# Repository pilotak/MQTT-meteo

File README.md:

# MQTT-meteo
STM32F103C8 (BluePill) based weather station. It can be either populated with Ethernet *(ENC28J60)* od WiFi *(ESP8266-01S)* module.

More info soon.

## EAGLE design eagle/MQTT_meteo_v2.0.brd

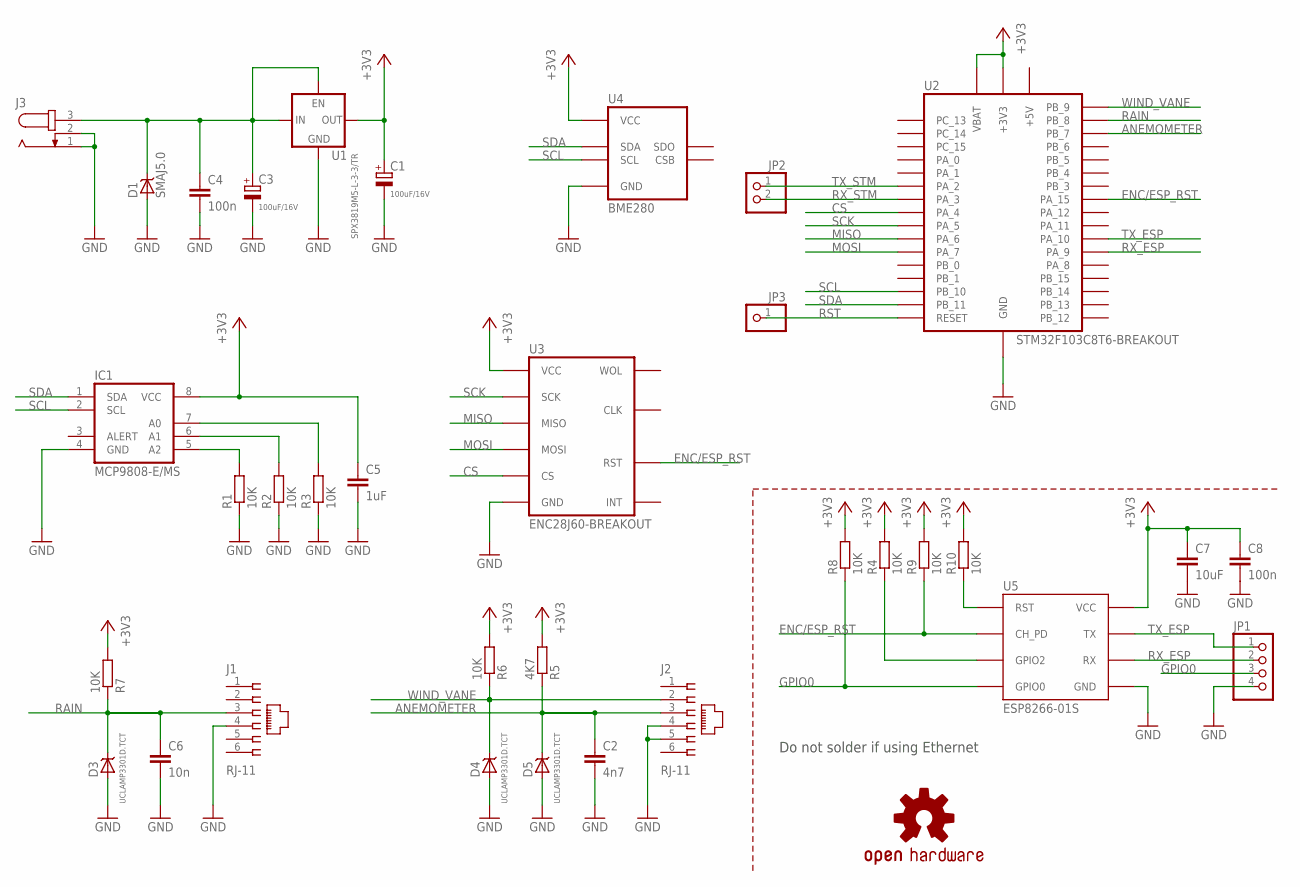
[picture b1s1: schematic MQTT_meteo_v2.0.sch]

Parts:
C1, C3: 100uF/16V; E2-5
C2: 4n7; C0805
C4, C8: 100n; C0805
C5: 1uF; C0805
C6: 10n; C0805
C7: 10uF; C0805
D1: SMAJ5.0; DO214AC
D3, D4, D5: UCLAMP3301D.TCT; SOD323
IC1: MCP9808-E/MS; MSOP8
J1, J2: RJ-11; 615006138421
J3: JACK-PLUG1; SPC4078
JP1: PINHD-1X4; 1X04
JP2: PINHD-1X2; 1X02
JP3: PINHD-1X01_2.54-90°; 1X01/90
LOGO1: OSHW-LOGOM-COPPER; OSHW-LOGO-M_COPPER
R1, R2, R3, R4, R6, R7, R8, R9, R10: 10K; R0805
R5: 4K7; R0805
U1: SPX3819M5-L-3-3/TR; SOT23-5
U2: STM32F103C8T6-BREAKOUT; STM32F103C8T6
U3: ENC28J60-BREAKOUT; ENC28J60
U4: BME280; BM*280
U5: ESP8266-01S; ESP-01

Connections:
+3V3: C1.+, C5.1, C7.1, C8.1, IC1.8 (VCC), R4.2, R5.2, R6.2, R7.2, R8.2, R9.2, R10.2, U1.5 (VOUT), U2.+3V3, U2.+3V3@1 (+3V3), U2.VBAT, U3.VCC, U4.VCC, U5.VCC
+5V: U2.+5V
ANEMOMETER: C2.1, D5.C, J2.3, R5.1, U2.PB_7
CS: U2.PA_4, U3.CS
ENC/ESP_RST: R9.1, U2.PA_15, U3.RST, U5.CH_PD
GND: C1.-, C2.2, C3.-, C4.2, C5.2, C6.2, C7.2, C8.2, D1.A, D3.A, D4.A, D5.A, IC1.4 (GND), J1.4, J2.4, J2.5, J3.1, J3.2, JP1.4, R1.1, R2.1, R3.1, U1.2 (GND), U2.GND, U2.GND@1 (GND), U2.GND@2 (GND), U3.GND, U4.GND, U5.GND
GPIO0: JP1.3, R8.1, U5.GPIO0
MISO: U2.PA_6, U3.SO (MISO)
MOSI: U2.PA_7, U3.SI (MOSI)
unnamed: R4.1, U5.GPIO2
unnamed: IC1.5 (A2), R1.2
unnamed: IC1.6 (A1), R2.2
unnamed: R10.1, U5.RST
unnamed: IC1.7 (A0), R3.2
RAIN: C6.1, D3.C, J1.3, R7.1, U2.PB_8
RST: JP3.1, U2.RESET
RX_ESP: JP1.2, U2.PA_9, U5.RX
RX_STM: JP2.2, U2.PA_3
SCK: U2.PA_5, U3.SCK
SCL: IC1.2 (SCL), U2.PB_10, U4.SCL
SDA: IC1.1 (SDA), U2.PB_11, U4.SDA
TX_ESP: JP1.1, U2.PA_10, U5.TX
TX_STM: JP2.1, U2.PA_2
VIN: C3.+, C4.1, D1.C, J3.3, U1.1 (VIN), U1.3 (EN)
WIND_VANE: D4.C, J2.2, R6.1, U2.PB_9

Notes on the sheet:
Do not solder if using Ethernet

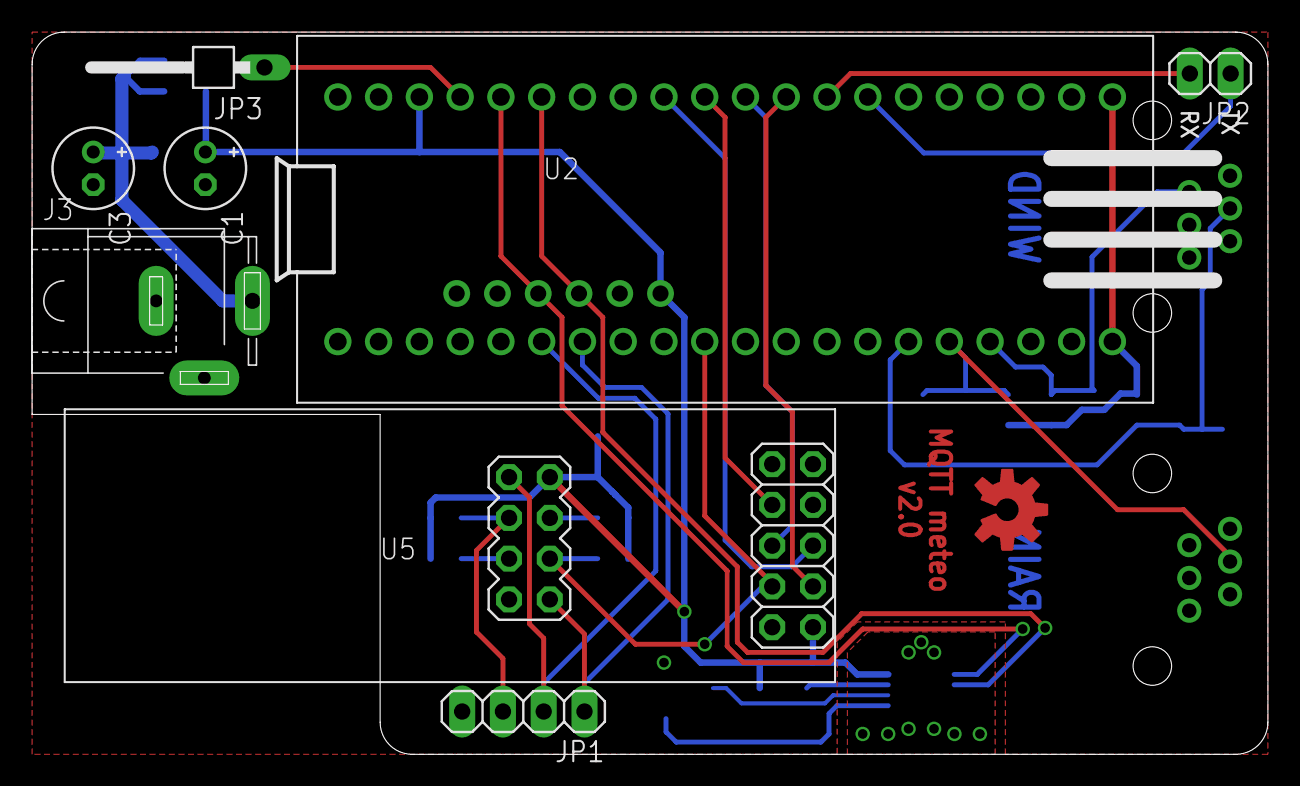
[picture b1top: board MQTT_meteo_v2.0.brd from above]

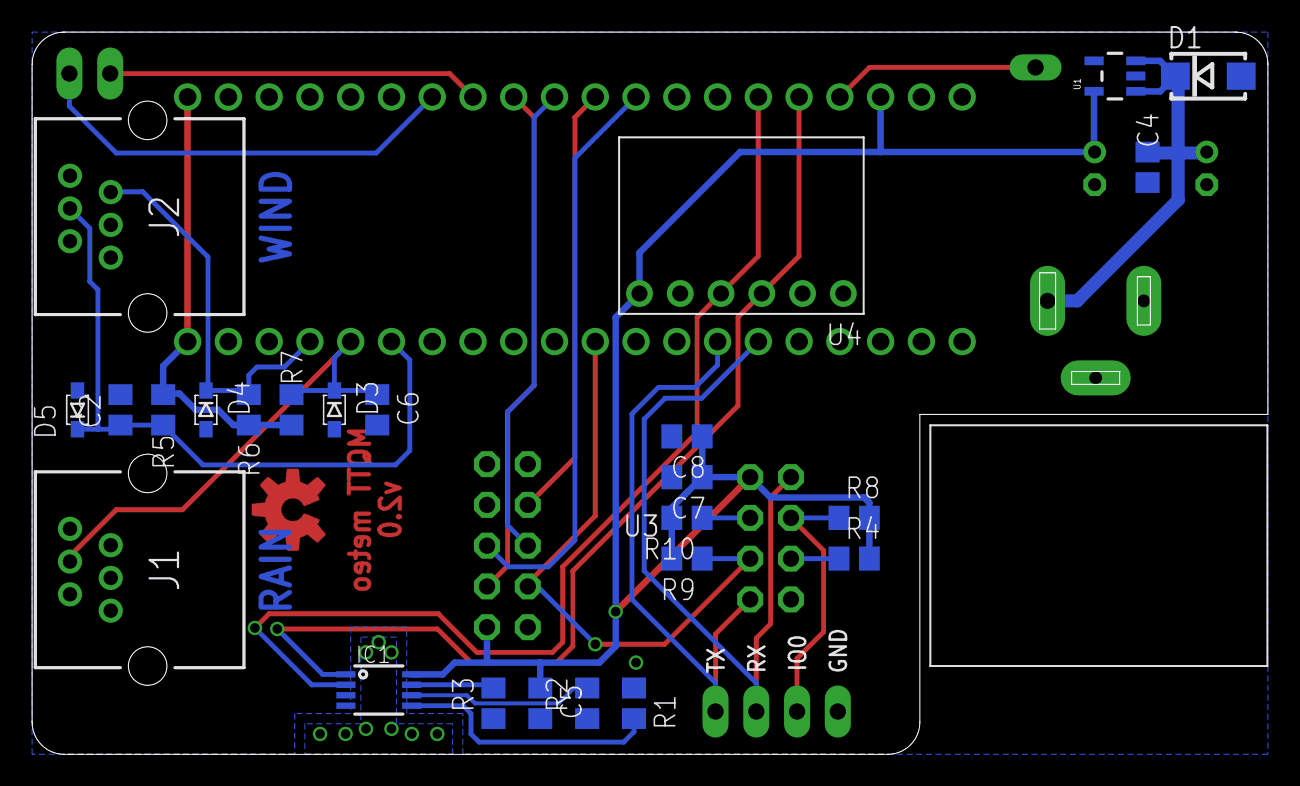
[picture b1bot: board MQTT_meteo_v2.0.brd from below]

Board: 2 copper layers, 77.0 x 45.0 mm, 35 parts (26 on the bottom side), 24 nets.

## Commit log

2018-05-07 init
2018-05-07 serial fix

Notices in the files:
parts and their libraries:
SparkFun-Aesthetics: Licensing: Creative Commons ShareAlike 4.0 International - https://creativecommons.org/licenses/by-sa/4.0
